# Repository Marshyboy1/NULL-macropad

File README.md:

## NULL-macropad
## The hackpad

This project was quite fun to build.
## Disclaimer
At the time of build I realised I have forgotten to put tolerances in the case therefore the PCB might have a really tight fit or won't fit at all. Please wait till I'm able to fix it or you can try fixing the file for yourself in cad.
## Schematic

## PCB Look

## PCB Design

## Firmware
This macropad uses QMK Firmaware

## Description
The NULL (pad) is a 4key macropad that has a rotary encoder, an oled display and can be fully customized based on your preferences.

* Keyboard Maintainer: [Matias](https://github.com/Marshyboy1)
* Hardware Supported: *This macropad uses and supports the seeed studio xiao RP2040, MX-Style switches, EC11 Rotary encoders and a  0.91 inch OLED display*
* Hardware Availability: *Just search up the names of the supported hardware. You'll find them directly and what costs fit your budget best based on shipping costs*

## BOM 
|--> 1x seeed studio rp2040

|--> 4x mx style switches-

|--> 1x EC11 Rotary Encoder

|--> 1x 0.91 inch oled display

|--> 4x M3x5x4 Heatset inserts

|--> 1x Case (1x 3d printed part)

|--> 4x M3x16mm screws(depends on how big your case is)

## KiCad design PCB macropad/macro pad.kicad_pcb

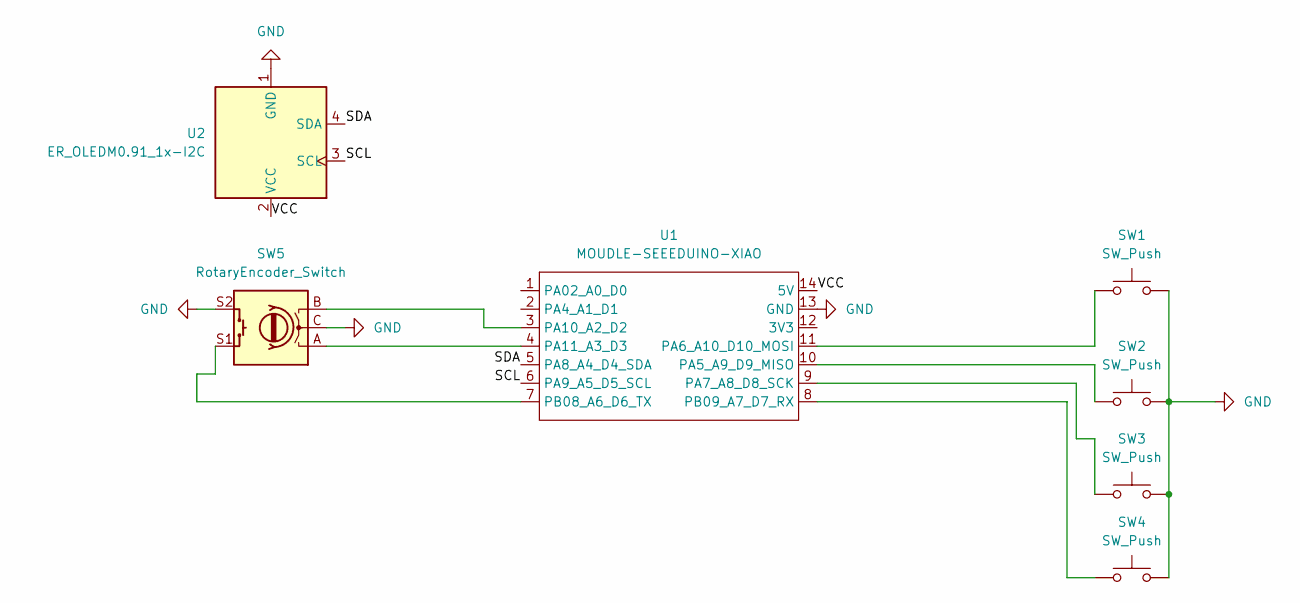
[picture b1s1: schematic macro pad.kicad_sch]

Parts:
SW1, SW2, SW3, SW4: SW_Push; SW_Cherry_MX_1.00u_PCB
SW5: RotaryEncoder_Switch; RotaryEncoder_Alps_EC11E-Switch_Vertical_H20mm
U1: MOUDLE-SEEEDUINO-XIAO; XIAO-Generic-Hybrid-14P-2.54-21X17.8MM
U2: ER_OLEDM0.91_1x-I2C

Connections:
/SCL: U1.6 (PA9_A5_D5_SCL), U2.3 (SCL)
/SDA: U1.5 (PA8_A4_D4_SDA), U2.4 (SDA)
/VCC: U1.14 (5V), U2.2 (VCC)
GND: SW1.2, SW2.2, SW3.2, SW4.2, SW5.C, SW5.S2, U1.13 (GND), U2.1 (GND)
unnamed: SW2.1, U1.10 (PA5_A9_D9_MISO)
unnamed: SW1.1, U1.11 (PA6_A10_D10_MOSI)
unnamed: SW3.1, U1.9 (PA7_A8_D8_SCK)
unnamed: SW5.B, U1.3 (PA10_A2_D2)
unnamed: SW5.A, U1.4 (PA11_A3_D3)
unnamed: SW5.S1, U1.7 (PB08_A6_D6_TX)
unnamed: SW4.1, U1.8 (PB09_A7_D7_RX)

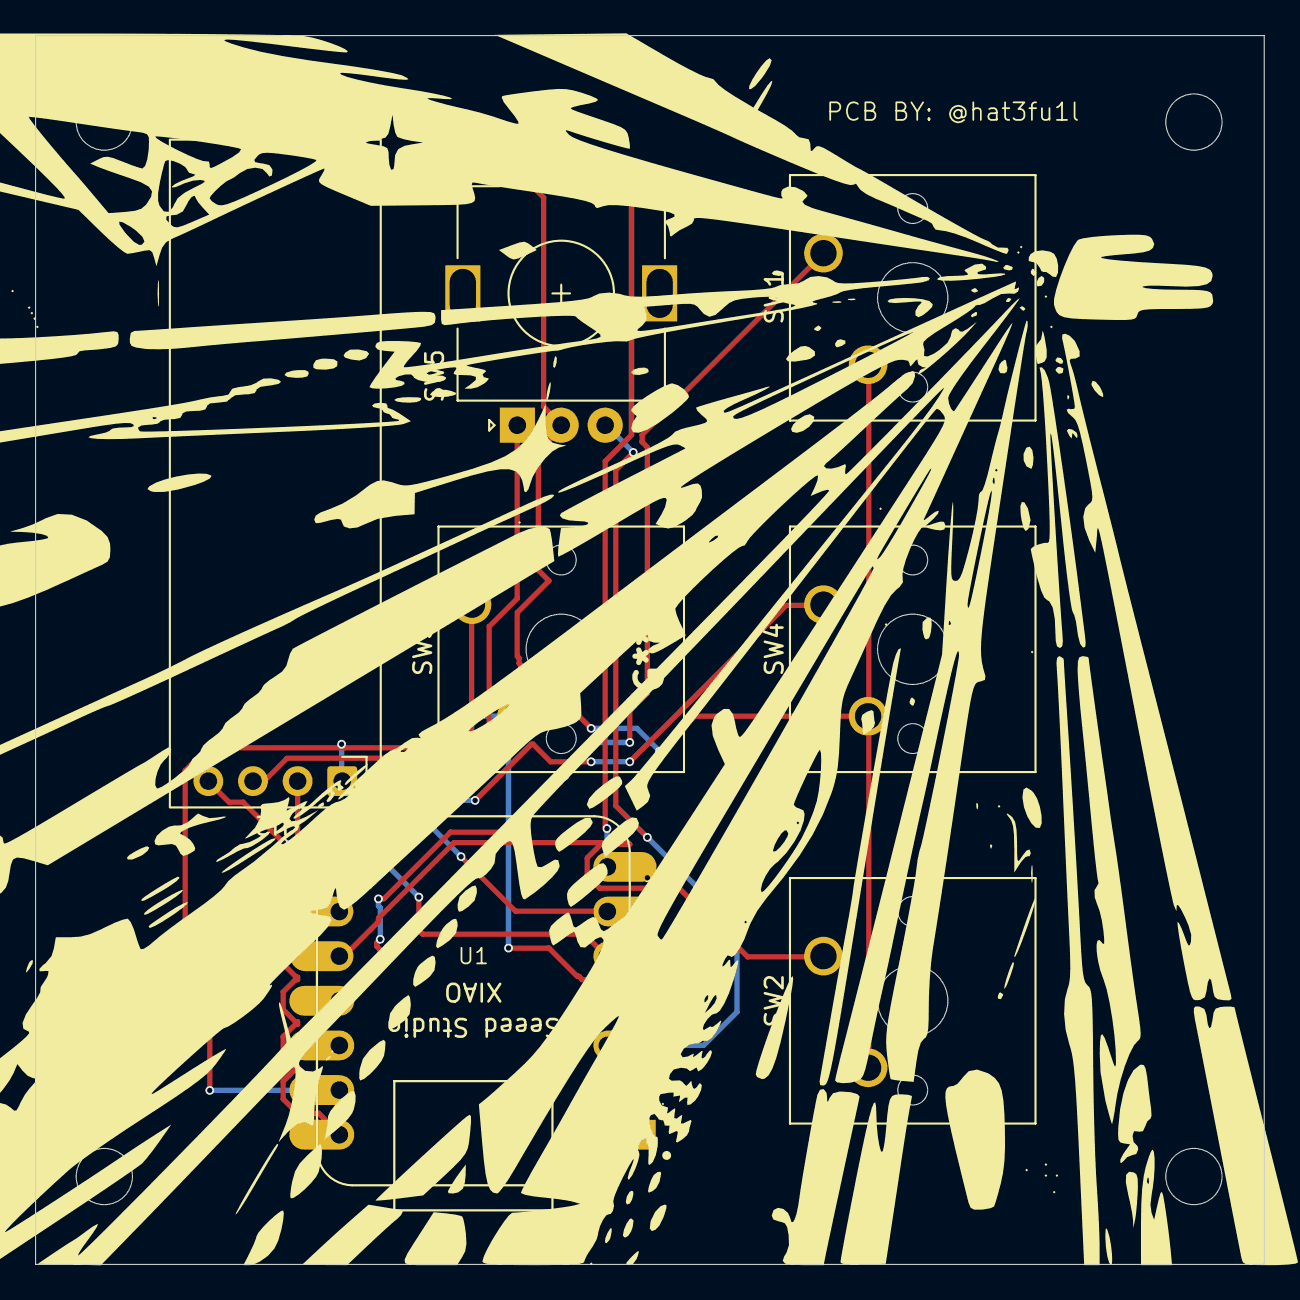
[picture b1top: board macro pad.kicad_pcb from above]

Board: 2 copper layers, 69.9 x 69.9 mm, 7 parts (0 on the bottom side), 11 nets.
